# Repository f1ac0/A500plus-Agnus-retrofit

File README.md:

# A500+ Agnus retrofit
I accidentally zapped my precious 8375 Agnus with ESD on my A500(+) rev8 motherboard, and I am planing to use a cheaper 8371 to continue the development of the Pistorm'X500 and other Amiga projects.

It is based on the same idea as the DietAgnus https://github.com/LIV2/Diet-Agnus-A500-plus except I plan to keep the PLCC84 socket to restore the original system later on. I am also looking forward modern replacement projects such as the ReAgnus https://github.com/jbilander/ReAgnus or https://github.com/jbilander/ReAgnus-MegAChip.

There are two versions in this repository :
- The Through Hole version was the first one I designed : it is based on a TH PLCC84 socket connected to a "plug" PCB using standard 2.54mm pin headers ; to ensure the contact with the motherboard socket, the plug PCB needs to mimic the PLCC "legs" with the addition of single core wires soldered from each top pad to its bottom counterpart all around the edges.
- The SMD version uses a SMD PLCC84 socket ; four strips of 1.27mm angled pin headers with a 0.46mm square section are used as contacts to the motherboard socket ; the spacer PCB(s) should help to solder the pins in place, push them on the contacts of the motherboard socket, and make it rigid enough to stay in place (stack two or 3 and glue them together).

These are not tested yet.

# Disclaimer
This is a hobbyist project, it comes with no warranty and no support. Also remember that the Amiga machines are about 30 years old and may fail because of such hardware expansions.

There are many Agnus versions and Amiga motherboards, so you really should look for information about the specific parts you plan to use.

I publish my work under the CC-BY-NC-SA license.

If you find it useful and want to reward my hard work : I am always looking for Amiga/Atari/Amstrad/Commodore/Sinclair/Thomson... to repair and hack, please contact me.

# Making it
Pull _XCLKEN to 5V using either a solder blob or a resistor.

If your Agnus is marked with VBB, install a 0.1uF ceramic cap on the TEST/VBB pin. Otherwise it may be closed to switch to NTSC.

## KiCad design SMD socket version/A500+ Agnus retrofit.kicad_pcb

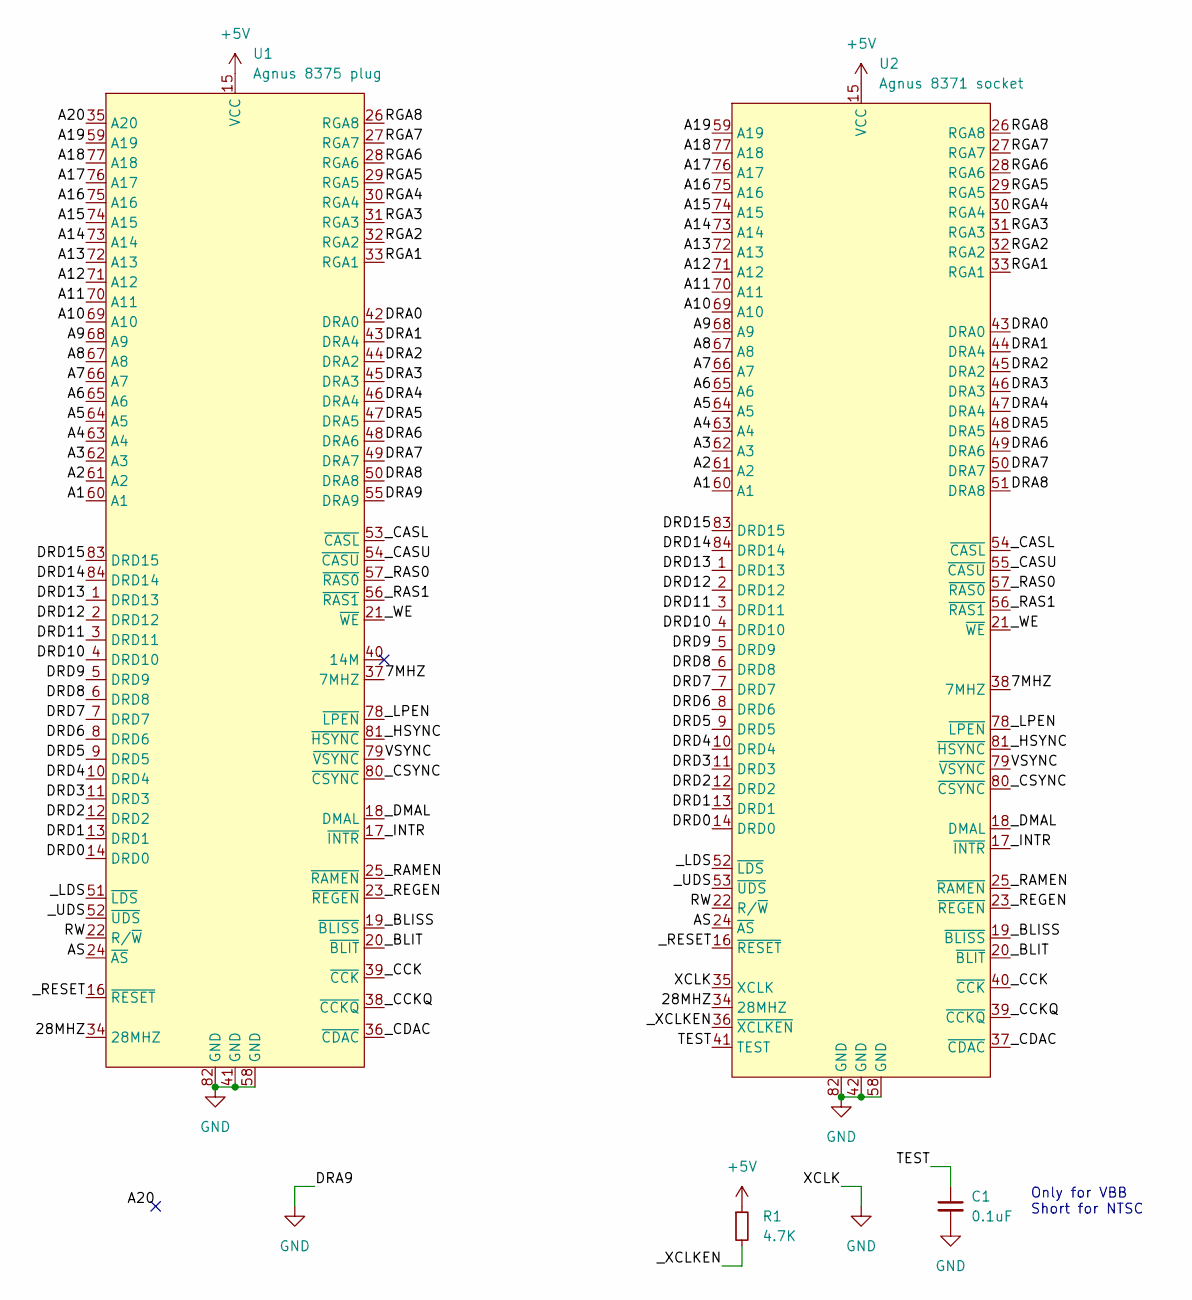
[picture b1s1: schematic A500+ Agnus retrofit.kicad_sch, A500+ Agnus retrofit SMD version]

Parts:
C1: 0.1uF; C_0805_2012Metric_shortable
R1: 4.7K; C_0805_2012Metric_shortable
U1: Agnus 8375 plug; PLCC-84_SMD-Plug
U2: Agnus 8371 socket; PLCC-84_SMD-Socket

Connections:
+5V: R1.1, U1.15 (VCC), U2.15 (VCC)
/7MHZ: U1.37 (7MHZ), U2.38 (7MHZ)
/28MHZ: U1.34 (28MHZ), U2.34 (28MHZ)
/A1: U1.60 (A1), U2.60 (A1)
/A2: U1.61 (A2), U2.61 (A2)
/A3: U1.62 (A3), U2.62 (A3)
/A4: U1.63 (A4), U2.63 (A4)
/A5: U1.64 (A5), U2.64 (A5)
/A6: U1.65 (A6), U2.65 (A6)
/A7: U1.66 (A7), U2.66 (A7)
/A8: U1.67 (A8), U2.67 (A8)
/A9: U1.68 (A9), U2.68 (A9)
/A10: U1.69 (A10), U2.69 (A10)
/A11: U1.70 (A11), U2.70 (A11)
/A12: U1.71 (A12), U2.71 (A12)
/A13: U1.72 (A13), U2.72 (A13)
/A14: U1.73 (A14), U2.73 (A14)
/A15: U1.74 (A15), U2.74 (A15)
/A16: U1.75 (A16), U2.75 (A16)
/A17: U1.76 (A17), U2.76 (A17)
/A18: U1.77 (A18), U2.77 (A18)
/A19: U1.59 (A19), U2.59 (A19)
/A20: U1.35 (A20)
/AS: U1.24 (~AS), U2.24 (~AS)
/DRA0: U1.42 (DRA0), U2.43 (DRA0)
/DRA1: U1.43 (DRA4), U2.44 (DRA4)
/DRA2: U1.44 (DRA2), U2.45 (DRA2)
/DRA3: U1.45 (DRA3), U2.46 (DRA3)
/DRA4: U1.46 (DRA4), U2.47 (DRA4)
/DRA5: U1.47 (DRA5), U2.48 (DRA5)
/DRA6: U1.48 (DRA6), U2.49 (DRA6)
/DRA7: U1.49 (DRA7), U2.50 (DRA7)
/DRA8: U1.50 (DRA8), U2.51 (DRA8)
/DRD0: U1.14 (DRD0), U2.14 (DRD0)
/DRD1: U1.13 (DRD1), U2.13 (DRD1)
/DRD2: U1.12 (DRD2), U2.12 (DRD2)
/DRD3: U1.11 (DRD3), U2.11 (DRD3)
/DRD4: U1.10 (DRD4), U2.10 (DRD4)
/DRD5: U1.9 (DRD5), U2.9 (DRD5)
/DRD6: U1.8 (DRD6), U2.8 (DRD6)
/DRD7: U1.7 (DRD7), U2.7 (DRD7)
/DRD8: U1.6 (DRD8), U2.6 (DRD8)
/DRD9: U1.5 (DRD9), U2.5 (DRD9)
/DRD10: U1.4 (DRD10), U2.4 (DRD10)
/DRD11: U1.3 (DRD11), U2.3 (DRD11)
/DRD12: U1.2 (DRD12), U2.2 (DRD12)
/DRD13: U1.1 (DRD13), U2.1 (DRD13)
/DRD14: U1.84 (DRD14), U2.84 (DRD14)
/DRD15: U1.83 (DRD15), U2.83 (DRD15)
/RGA1: U1.33 (RGA1), U2.33 (RGA1)
/RGA2: U1.32 (RGA2), U2.32 (RGA2)
/RGA3: U1.31 (RGA3), U2.31 (RGA3)
/RGA4: U1.30 (RGA4), U2.30 (RGA4)
/RGA5: U1.29 (RGA5), U2.29 (RGA5)
/RGA6: U1.28 (RGA6), U2.28 (RGA6)
/RGA7: U1.27 (RGA7), U2.27 (RGA7)
/RGA8: U1.26 (RGA8), U2.26 (RGA8)
/RW: U1.22 (R/~W), U2.22 (R/~W)
/TEST: C1.1, U2.41 (TEST)
/VSYNC: U1.79 (~VSYNC), U2.79 (~VSYNC)
/_BLISS: U1.19 (~BLISS), U2.19 (~BLISS)
/_BLIT: U1.20 (~BLIT), U2.20 (~BLIT)
/_CASL: U1.53 (~CASL), U2.54 (~CASL)
/_CASU: U1.54 (~CASU), U2.55 (~CASU)
/_CCK: U1.39 (~CCK), U2.40 (~CCK)
/_CCKQ: U1.38 (~CCKQ), U2.39 (~CCKQ)
/_CDAC: U1.36 (~CDAC), U2.37 (~CDAC)
/_CSYNC: U1.80 (~CSYNC), U2.80 (~CSYNC)
/_DMAL: U1.18 (DMAL), U2.18 (DMAL)
/_HSYNC: U1.81 (~HSYNC), U2.81 (~HSYNC)
/_INTR: U1.17 (~INTR), U2.17 (~INTR)
/_LDS: U1.51 (~LDS), U2.52 (~LDS)
/_LPEN: U1.78 (~LPEN), U2.78 (~LPEN)
/_RAMEN: U1.25 (~RAMEN), U2.25 (~RAMEN)
/_RAS0: U1.57 (~RAS0), U2.57 (~RAS0)
/_RAS1: U1.56 (~RAS1), U2.56 (~RAS1)
/_REGEN: U1.23 (~REGEN), U2.23 (~REGEN)
/_RESET: U1.16 (~RESET), U2.16 (~RESET)
/_UDS: U1.52 (~UDS), U2.53 (~UDS)
/_WE: U1.21 (~WE), U2.21 (~WE)
/_XCLKEN: R1.2, U2.36 (~XCLKEN)
GND: C1.2, U1.41 (GND), U1.55 (DRA9), U1.58 (GND), U1.82 (GND), U2.35 (XCLK), U2.42 (GND), U2.58 (GND), U2.82 (GND)

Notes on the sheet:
Only for VBB Short for NTSC

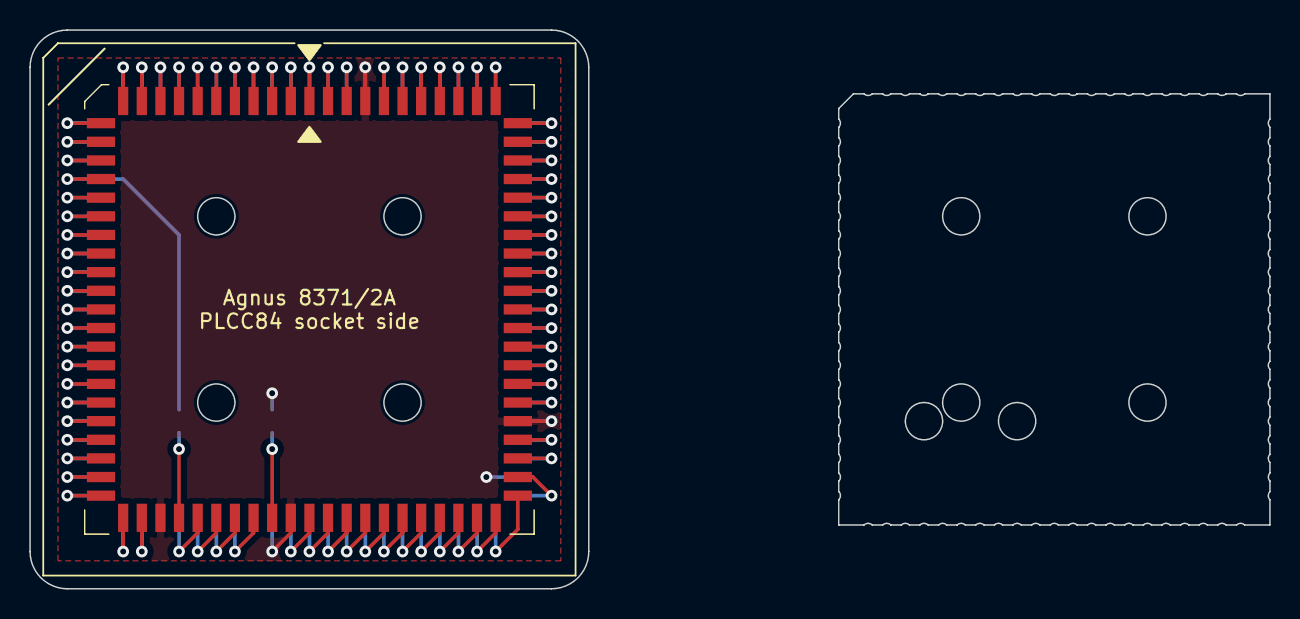
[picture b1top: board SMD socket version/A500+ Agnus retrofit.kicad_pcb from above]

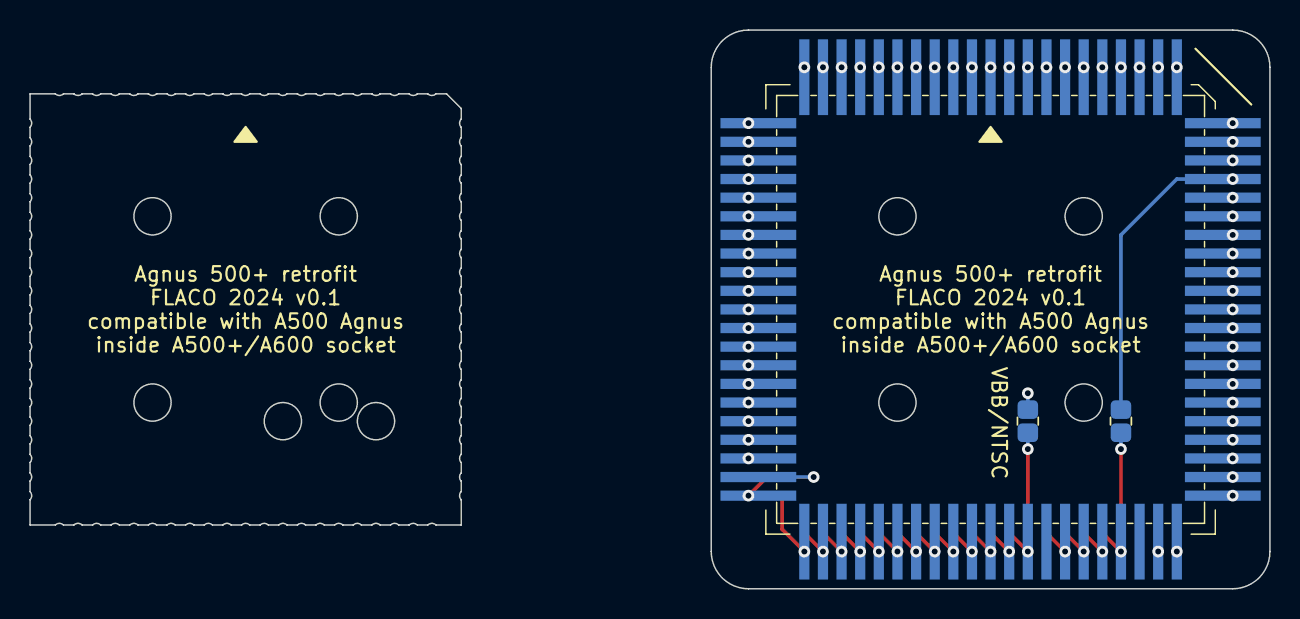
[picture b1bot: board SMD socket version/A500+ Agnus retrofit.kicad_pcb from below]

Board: 2 copper layers, 84.6 x 38.1 mm, 4 parts (3 on the bottom side), 81 nets.

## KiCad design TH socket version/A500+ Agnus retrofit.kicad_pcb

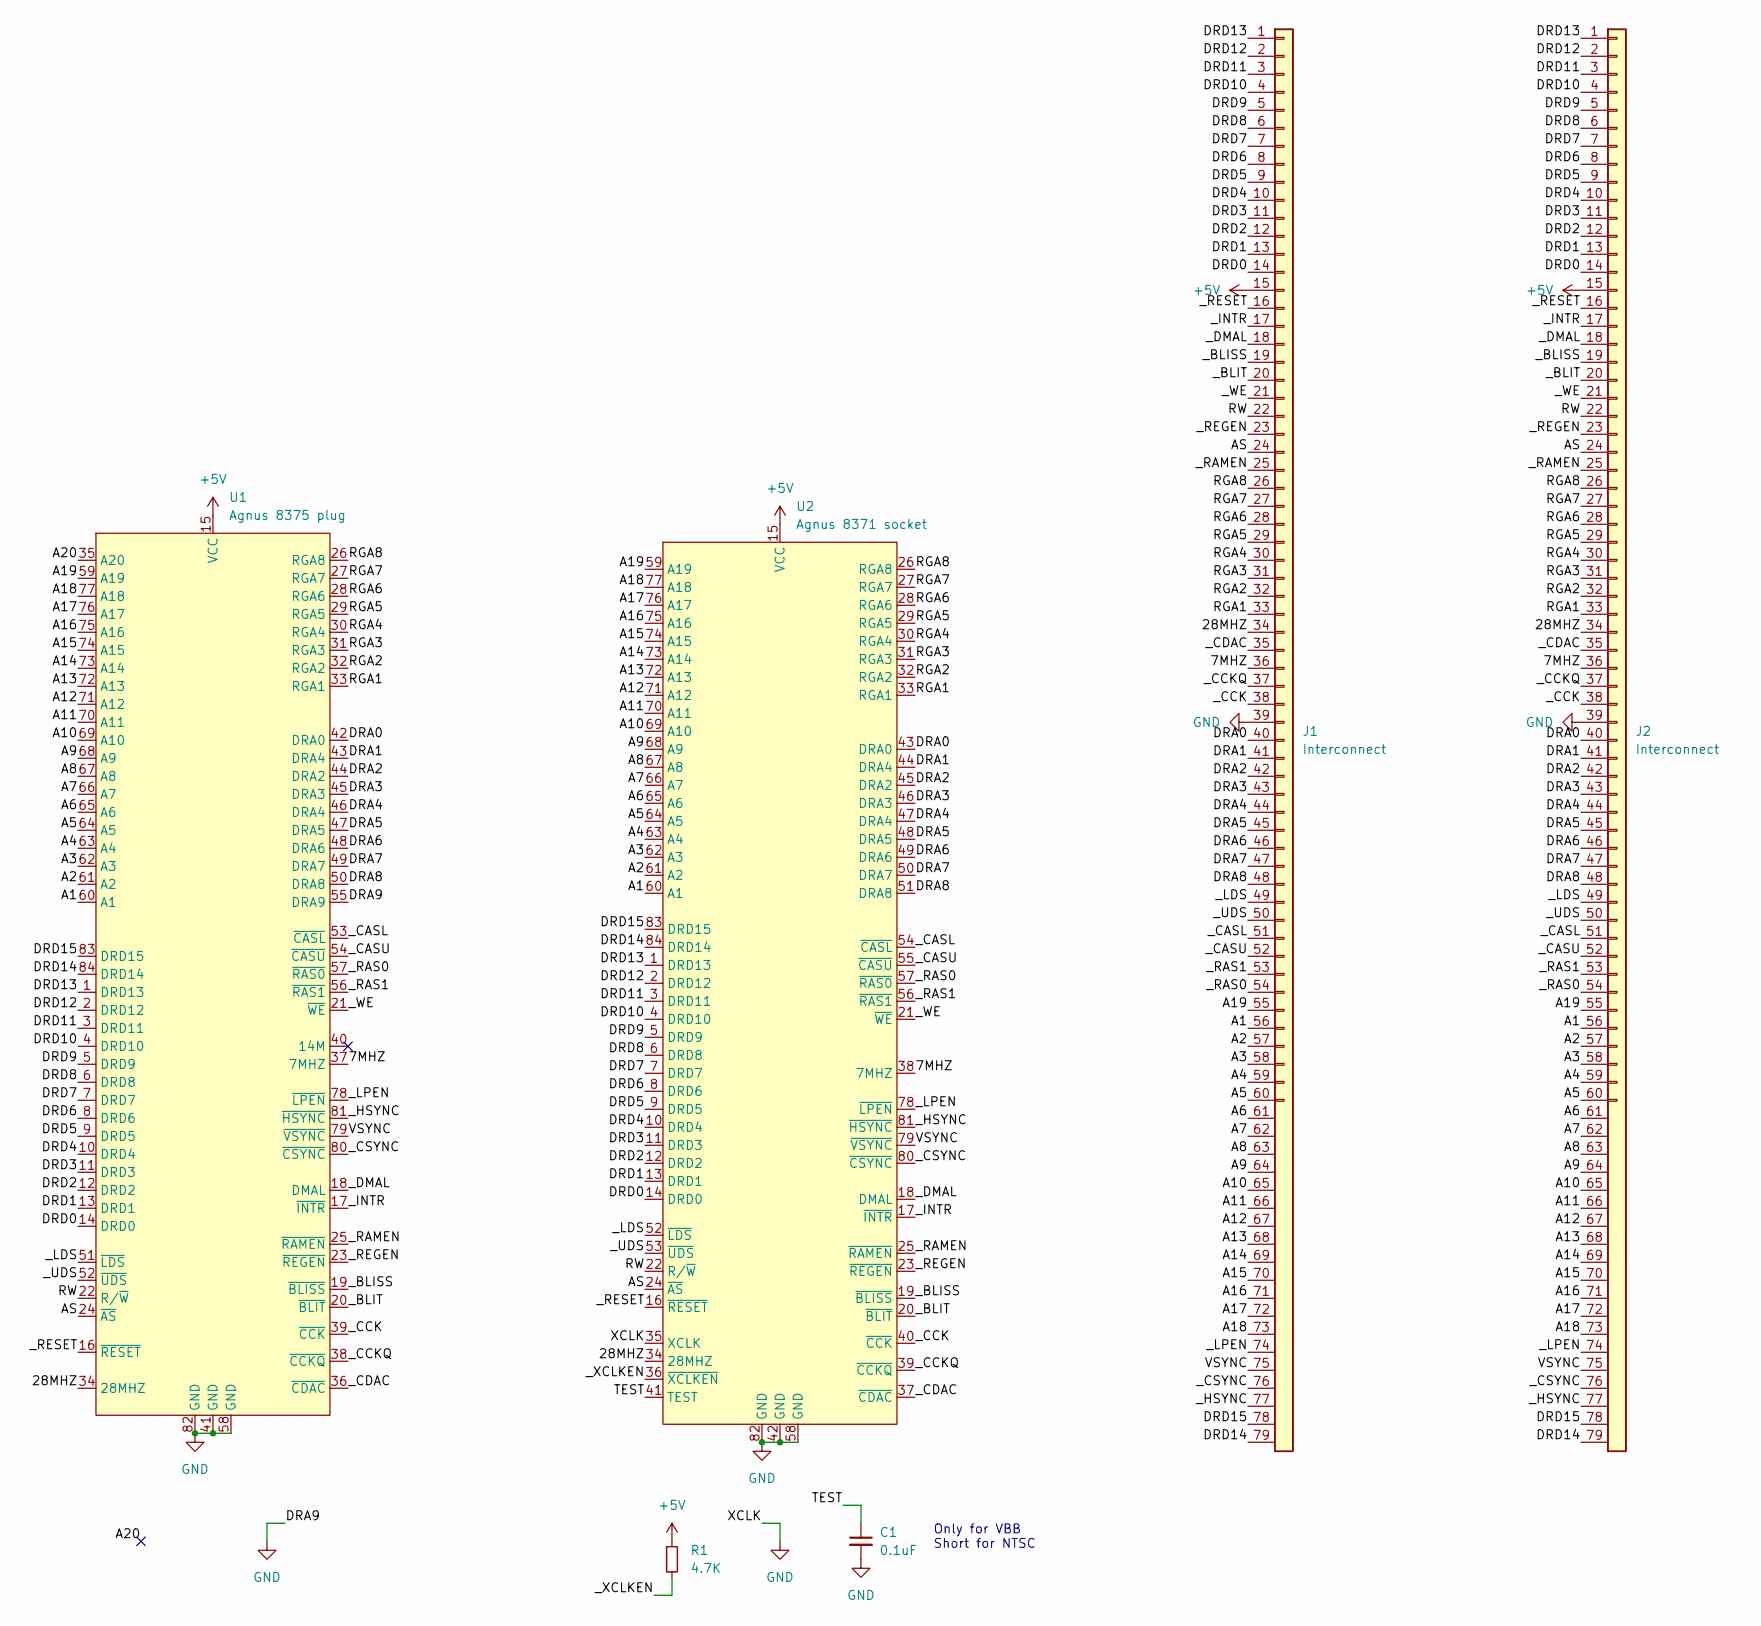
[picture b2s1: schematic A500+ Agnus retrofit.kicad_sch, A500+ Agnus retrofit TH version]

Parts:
C1: 0.1uF; C_0805_2012Metric_shortable
J1, J2: Interconnect; A500+_Agnus_retrofit_interconnect
R1: 4.7K; C_0805_2012Metric_shortable
U1: Agnus 8375 plug; A500+_Agnus_retrofit_plug
U2: Agnus 8371 socket; PLCC-84_THT-Socket

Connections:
+5V: J1.15, J2.15, R1.1, U1.15 (VCC), U2.15 (VCC)
/7MHZ: J1.36, J2.36, U1.37 (7MHZ), U2.38 (7MHZ)
/28MHZ: J1.34, J2.34, U1.34 (28MHZ), U2.34 (28MHZ)
/A1: J1.56, J2.56, U1.60 (A1), U2.60 (A1)
/A2: J1.57, J2.57, U1.61 (A2), U2.61 (A2)
/A3: J1.58, J2.58, U1.62 (A3), U2.62 (A3)
/A4: J1.59, J2.59, U1.63 (A4), U2.63 (A4)
/A5: J1.60, J2.60, U1.64 (A5), U2.64 (A5)
/A6: J1.61 (Pin_41), J2.61 (Pin_41), U1.65 (A6), U2.65 (A6)
/A7: J1.62 (Pin_42), J2.62 (Pin_42), U1.66 (A7), U2.66 (A7)
/A8: J1.63 (Pin_43), J2.63 (Pin_43), U1.67 (A8), U2.67 (A8)
/A9: J1.64 (Pin_44), J2.64 (Pin_44), U1.68 (A9), U2.68 (A9)
/A10: J1.65 (Pin_45), J2.65 (Pin_45), U1.69 (A10), U2.69 (A10)
/A11: J1.66 (Pin_46), J2.66 (Pin_46), U1.70 (A11), U2.70 (A11)
/A12: J1.67 (Pin_47), J2.67 (Pin_47), U1.71 (A12), U2.71 (A12)
/A13: J1.68 (Pin_48), J2.68 (Pin_48), U1.72 (A13), U2.72 (A13)
/A14: J1.69 (Pin_49), J2.69 (Pin_49), U1.73 (A14), U2.73 (A14)
/A15: J1.70 (Pin_50), J2.70 (Pin_50), U1.74 (A15), U2.74 (A15)
/A16: J1.71 (Pin_51), J2.71 (Pin_51), U1.75 (A16), U2.75 (A16)
/A17: J1.72 (Pin_52), J2.72 (Pin_52), U1.76 (A17), U2.76 (A17)
/A18: J1.73 (Pin_53), J2.73 (Pin_53), U1.77 (A18), U2.77 (A18)
/A19: J1.55, J2.55, U1.59 (A19), U2.59 (A19)
/A20: U1.35 (A20)
/AS: J1.24, J2.24, U1.24 (~AS), U2.24 (~AS)
/DRA0: J1.40, J2.40, U1.42 (DRA0), U2.43 (DRA0)
/DRA1: J1.41, J2.41, U1.43 (DRA4), U2.44 (DRA4)
/DRA2: J1.42, J2.42, U1.44 (DRA2), U2.45 (DRA2)
/DRA3: J1.43, J2.43, U1.45 (DRA3), U2.46 (DRA3)
/DRA4: J1.44, J2.44, U1.46 (DRA4), U2.47 (DRA4)
/DRA5: J1.45, J2.45, U1.47 (DRA5), U2.48 (DRA5)
/DRA6: J1.46, J2.46, U1.48 (DRA6), U2.49 (DRA6)
/DRA7: J1.47, J2.47, U1.49 (DRA7), U2.50 (DRA7)
/DRA8: J1.48, J2.48, U1.50 (DRA8), U2.51 (DRA8)
/DRD0: J1.14, J2.14, U1.14 (DRD0), U2.14 (DRD0)
/DRD1: J1.13, J2.13, U1.13 (DRD1), U2.13 (DRD1)
/DRD2: J1.12, J2.12, U1.12 (DRD2), U2.12 (DRD2)
/DRD3: J1.11, J2.11, U1.11 (DRD3), U2.11 (DRD3)
/DRD4: J1.10, J2.10, U1.10 (DRD4), U2.10 (DRD4)
/DRD5: J1.9, J2.9, U1.9 (DRD5), U2.9 (DRD5)
/DRD6: J1.8, J2.8, U1.8 (DRD6), U2.8 (DRD6)
/DRD7: J1.7, J2.7, U1.7 (DRD7), U2.7 (DRD7)
/DRD8: J1.6, J2.6, U1.6 (DRD8), U2.6 (DRD8)
/DRD9: J1.5, J2.5, U1.5 (DRD9), U2.5 (DRD9)
/DRD10: J1.4, J2.4, U1.4 (DRD10), U2.4 (DRD10)
/DRD11: J1.3, J2.3, U1.3 (DRD11), U2.3 (DRD11)
/DRD12: J1.2, J2.2, U1.2 (DRD12), U2.2 (DRD12)
/DRD13: J1.1, J2.1, U1.1 (DRD13), U2.1 (DRD13)
/DRD14: J1.79 (Pin_58), J2.79 (Pin_58), U1.84 (DRD14), U2.84 (DRD14)
/DRD15: J1.78 (Pin_58), J2.78 (Pin_58), U1.83 (DRD15), U2.83 (DRD15)
/RGA1: J1.33, J2.33, U1.33 (RGA1), U2.33 (RGA1)
/RGA2: J1.32, J2.32, U1.32 (RGA2), U2.32 (RGA2)
/RGA3: J1.31, J2.31, U1.31 (RGA3), U2.31 (RGA3)
/RGA4: J1.30, J2.30, U1.30 (RGA4), U2.30 (RGA4)
/RGA5: J1.29, J2.29, U1.29 (RGA5), U2.29 (RGA5)
/RGA6: J1.28, J2.28, U1.28 (RGA6), U2.28 (RGA6)
/RGA7: J1.27, J2.27, U1.27 (RGA7), U2.27 (RGA7)
/RGA8: J1.26, J2.26, U1.26 (RGA8), U2.26 (RGA8)
/RW: J1.22, J2.22, U1.22 (R/~W), U2.22 (R/~W)
/TEST: C1.1, U2.41 (TEST)
/VSYNC: J1.75 (Pin_55), J2.75 (Pin_55), U1.79 (~VSYNC), U2.79 (~VSYNC)
/_BLISS: J1.19, J2.19, U1.19 (~BLISS), U2.19 (~BLISS)
/_BLIT: J1.20, J2.20, U1.20 (~BLIT), U2.20 (~BLIT)
/_CASL: J1.51, J2.51, U1.53 (~CASL), U2.54 (~CASL)
/_CASU: J1.52, J2.52, U1.54 (~CASU), U2.55 (~CASU)
/_CCK: J1.38, J2.38, U1.39 (~CCK), U2.40 (~CCK)
/_CCKQ: J1.37, J2.37, U1.38 (~CCKQ), U2.39 (~CCKQ)
/_CDAC: J1.35, J2.35, U1.36 (~CDAC), U2.37 (~CDAC)
/_CSYNC: J1.76 (Pin_56), J2.76 (Pin_56), U1.80 (~CSYNC), U2.80 (~CSYNC)
/_DMAL: J1.18, J2.18, U1.18 (DMAL), U2.18 (DMAL)
/_HSYNC: J1.77 (Pin_57), J2.77 (Pin_57), U1.81 (~HSYNC), U2.81 (~HSYNC)
/_INTR: J1.17, J2.17, U1.17 (~INTR), U2.17 (~INTR)
/_LDS: J1.49, J2.49, U1.51 (~LDS), U2.52 (~LDS)
/_LPEN: J1.74 (Pin_54), J2.74 (Pin_54), U1.78 (~LPEN), U2.78 (~LPEN)
/_RAMEN: J1.25, J2.25, U1.25 (~RAMEN), U2.25 (~RAMEN)
/_RAS0: J1.54, J2.54, U1.57 (~RAS0), U2.57 (~RAS0)
/_RAS1: J1.53, J2.53, U1.56 (~RAS1), U2.56 (~RAS1)
/_REGEN: J1.23, J2.23, U1.23 (~REGEN), U2.23 (~REGEN)
/_RESET: J1.16, J2.16, U1.16 (~RESET), U2.16 (~RESET)
/_UDS: J1.50, J2.50, U1.52 (~UDS), U2.53 (~UDS)
/_WE: J1.21, J2.21, U1.21 (~WE), U2.21 (~WE)
/_XCLKEN: R1.2, U2.36 (~XCLKEN)
GND: C1.2, J1.39, J2.39, U1.41 (GND), U1.55 (DRA9), U1.58 (GND), U1.82 (GND), U2.35 (XCLK), U2.42 (GND), U2.58 (GND), U2.82 (GND)

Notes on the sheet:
Only for VBB Short for NTSC

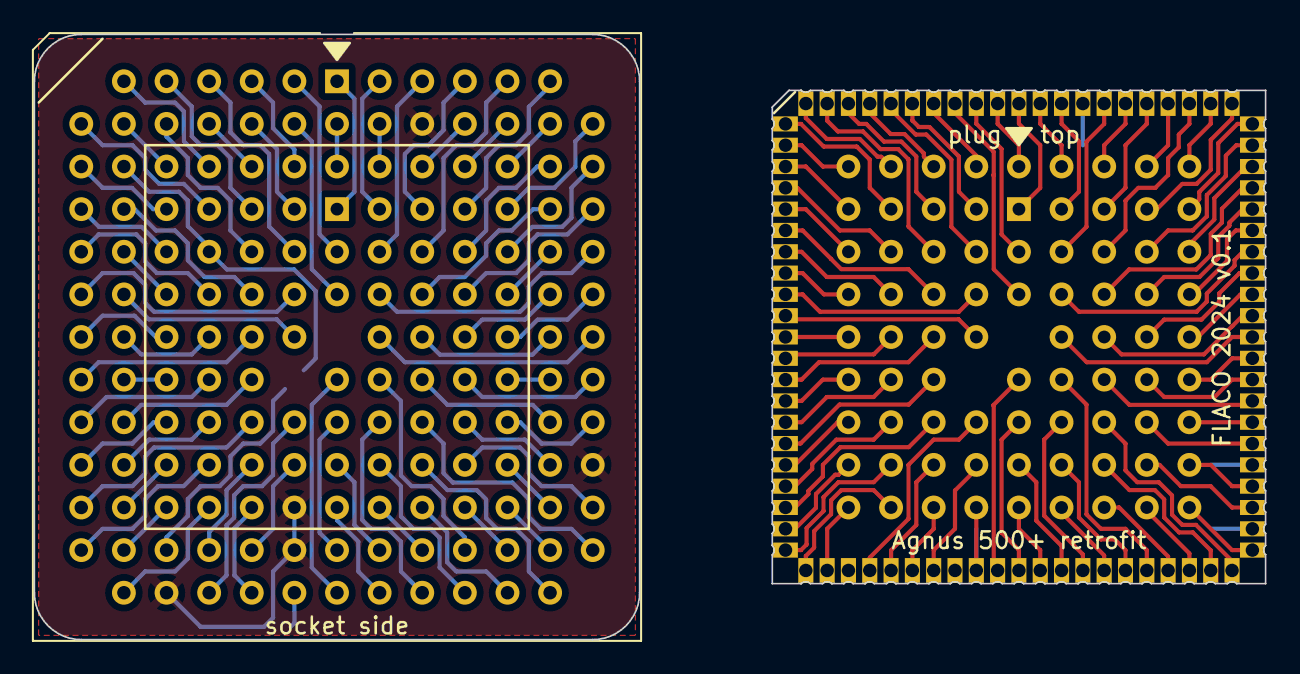
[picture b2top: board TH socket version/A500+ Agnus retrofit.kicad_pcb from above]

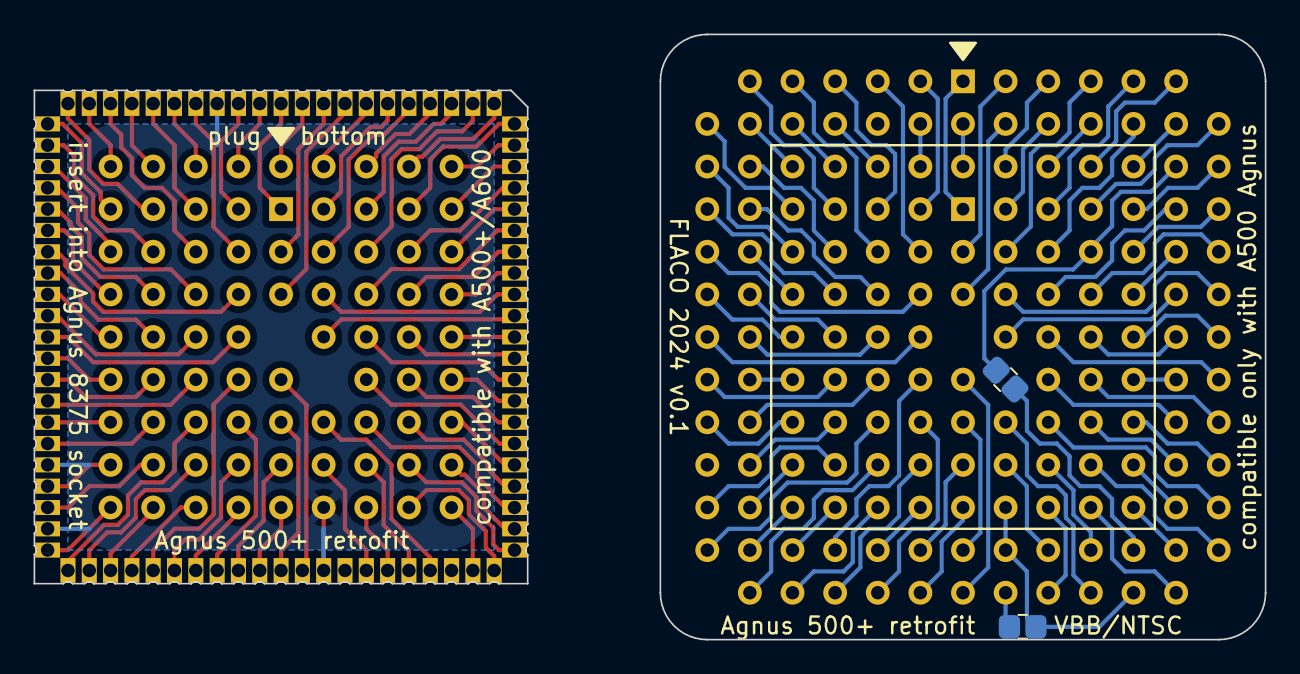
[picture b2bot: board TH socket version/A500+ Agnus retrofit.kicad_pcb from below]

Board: 2 copper layers, 73.4 x 36.1 mm, 6 parts (2 on the bottom side), 81 nets.

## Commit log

2024-03-07 Repository init with KiCad files, Readme and License

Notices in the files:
SMD socket version/A500+ Agnus retrofit.kicad_pcb:
FLACO 2024 CC-BY-NC-SA
